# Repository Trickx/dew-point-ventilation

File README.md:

***

# Dew Point Ventilation

**Ventilation is the best and cheapest measure against damp cellars - at least if done right.
In this project, an ESP8266 (NodeMCU) monitors dew points from the inside and outside and activates up to 4 fans to transport the moisture in the air to the outside.**

This project is inspired by 2 articles by the German Make magazine: [Taupunktlüfter](https://github.com/MakeMagazinDE/Taupunktluefter) and [Zirkulationspumpensteuerung](https://github.com/MakeMagazinDE/Zirkulationspumpensteuerung)
Instead of their Arduino approach, this projects makes use of ESP8266 and [Tasmota](https://github.com/arendst/Tasmota).

**Note: I don't take over any risk, nor responsibility for anything. If you decide to reproduce this project you will be killed by hardware or software.**

A PCB was designed with Autodesk's Eagle. The PCB is currently under test, so be aware.

**Diffs from original designs by Make:**
- NodeMCUs instead of Arduino
- Tasmota and Script instead of Arduino coding
- 4 Outputs via solid state relais
- Multiple Sensor options:
- 1Wire
- I2C
- AM230x

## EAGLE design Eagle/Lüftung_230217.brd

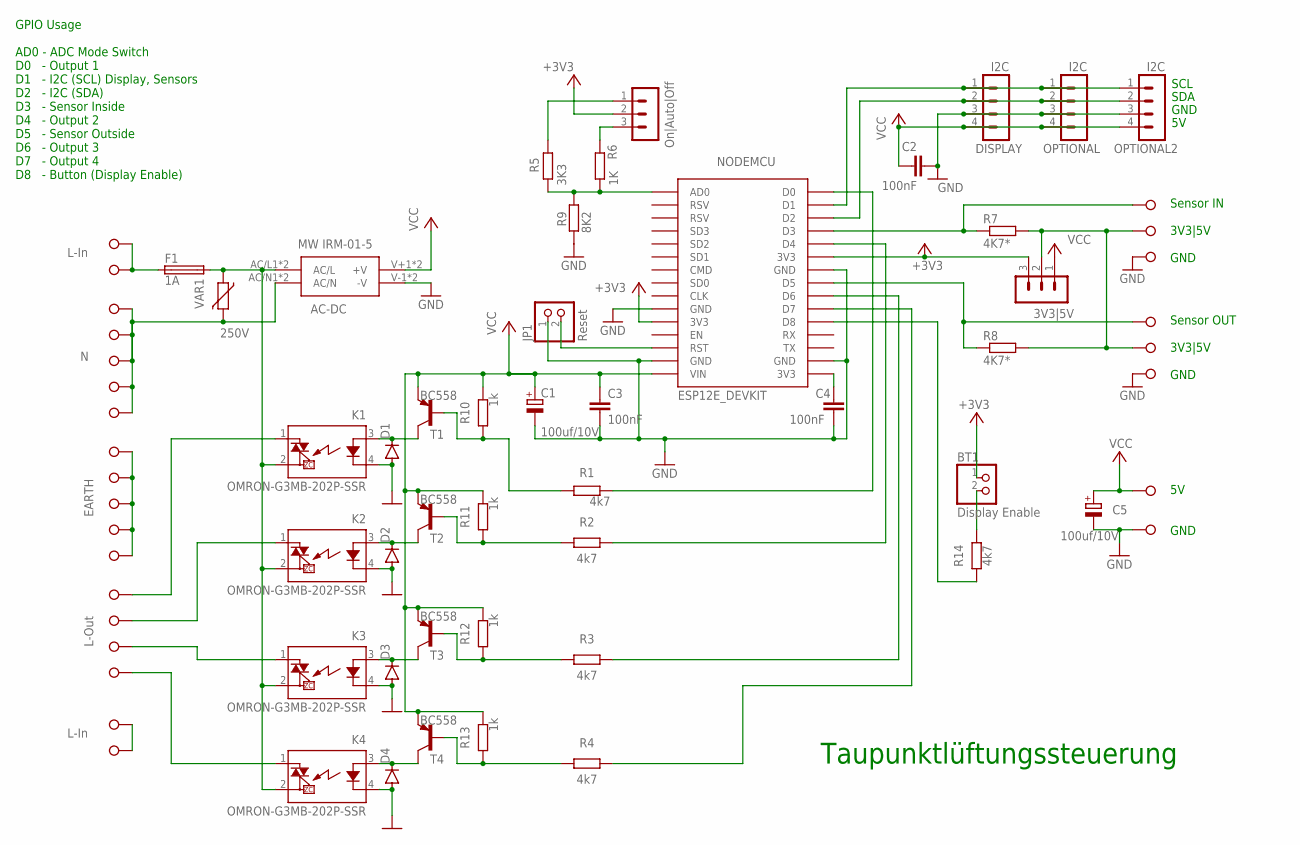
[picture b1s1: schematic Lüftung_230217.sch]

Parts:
5V|3V3: 3V3|5V; LüFTUNG_230217_2_CON-LSTB_MA03-1
AC-DC: MW IRM-01-5; LüFTUNG_230217_2_SAMACSYS_PARTS_IRM015
BT1: Display Enable; LüFTUNG_230217_2_PINHEAD_1X02
C1, C5: 100uf/10V; LüFTUNG_230217_2_MY_RCL_E2,5-7
C2, C3, C4: 100nF; LüFTUNG_230217_2_CAPACITOR-WIMA_C5B3.5
D1: LüFTUNG_230217_2_DIODE_1N4148; LüFTUNG_230217_2_DIODE_D-5
D2, D3, D4: LüFTUNG_230217_2_DIODE_1N4148DO35-7; LüFTUNG_230217_2_DIODE_DO35-7
DISPLAY: I2C; LüFTUNG_230217_2_CON-LSTB_MA04-1
F1: 1A; LüFTUNG_230217_2_MY_FUSE_SH22,5
JP1: Reset; LüFTUNG_230217_2_PINHEAD_1X02
K1, K2, K3, K4: OMRON-G3MB-202P-SSR; LüFTUNG_230217_2_OMRON-G3MB-202P-SSR_OMRON-G3MB-202P-SSR
NODEMCU: ESP12E_DEVKIT; LüFTUNG_230217_2_ESP12E_DEVKIT_ESP12E_DEVKIT
OPTIONAL, OPTIONAL2: I2C; LüFTUNG_230217_2_CON-LSTB_MA04-1
R1, R2, R3, R4, R14: 4k7; LüFTUNG_230217_2_MY_RCL_0207/10
R5: 3K3; LüFTUNG_230217_2_MY_RCL_0204V
R6: 1K; LüFTUNG_230217_2_MY_RCL_0204V
R7, R8: 4K7*; LüFTUNG_230217_2_MY_RCL_0207/10
R9: 8K2; LüFTUNG_230217_2_MY_RCL_0204V
R10, R11, R12, R13: 1k; LüFTUNG_230217_2_MY_RCL_0207/10
SWITCH: On|Auto|Off; LüFTUNG_230217_2_CON-LSTB_MA03-1
T1, T2, T3, T4: BC558; LüFTUNG_230217_2_TRANSISTOR-NEU-TO92_TO92
VAR1: 250V; LüFTUNG_230217_2_MY_VARISTOR_R-5
X1, X18: L-In; CON-WAGO-508_W236-1
X2, X17: L-In; CON-WAGO-508_W236-NOCAP
X3: N; CON-WAGO-508_W236-1
X4, X5, X6, X7: N; CON-WAGO-508_W236-NOCAP
X8: EARTH; CON-WAGO-508_W236-1
X9, X10, X11, X12: EARTH; CON-WAGO-508_W236-NOCAP
X13: L-Out; CON-WAGO-508_W236-1
X14, X15, X16: L-Out; CON-WAGO-508_W236-NOCAP
X19: Sensor-In; CON-WAGO-508_W236-NOCAP
X20, X23: 3V3; CON-WAGO-508_W236-NOCAP
X21, X24: GND; CON-WAGO-508_W236-1
X22: Sensor-Out; CON-WAGO-508_W236-NOCAP
X25: GND; CON-WAGO-508_W236-NOCAP
X26: VCC; CON-WAGO-508_W236-1

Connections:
230V-SWITCH: X17.1, X17.2, X18.1, X18.2
+3V3: 5V|3V3.3, BT1.1, NODEMCU.3V3@0 (3V3), NODEMCU.3V3@1 (3V3), SWITCH.2
EARTH: X8.1, X8.2, X9.1, X9.2, X10.1, X10.2, X11.1, X11.2, X12.1, X12.2
GND: AC-DC.V-1 (-V), AC-DC.V-2 (-V), C1.-, C2.2, C3.2, C4.2, C5.-, D1.A, D2.A, D3.A, D4.A, DISPLAY.3, JP1.1, K1.4 (K), K2.4 (K), K3.4 (K), K4.4 (K), NODEMCU.GND@0 (GND), NODEMCU.GND@1 (GND), NODEMCU.GND@2 (GND), NODEMCU.GND@3 (GND), OPTIONAL.3, OPTIONAL2.3, R9.2, X21.1, X21.2, X24.1, X24.2, X25.1, X25.2
L: F1.1, X1.1, X1.2, X2.1, X2.2
L2: K2.1 (DS1), X14.1, X14.2
L3: K3.1 (DS1), X15.1, X15.2
L4: K4.1 (DS1), X16.1, X16.2
L-OUT: K1.1 (DS1), X13.1, X13.2
LF: AC-DC.AC/L1 (AC/L), AC-DC.AC/L2 (AC/L), F1.2, K1.2 (DS2), K2.2 (DS2), K3.2 (DS2), K4.2 (DS2), VAR1.1
N: AC-DC.AC/N1 (AC/N), AC-DC.AC/N2 (AC/N), VAR1.2, X3.1, X3.2, X4.1, X4.2, X5.1, X5.2, X6.1, X6.2, X7.1, X7.2
unnamed: DISPLAY.1, NODEMCU.D1, OPTIONAL.1, OPTIONAL2.1
unnamed: R1.2, R10.2, T1.2 (B)
unnamed: NODEMCU.D5, R8.1, X22.1, X22.2
unnamed: D1.C, K1.3 (A), T1.3 (C)
unnamed: NODEMCU.D0, R1.1
unnamed: 5V|3V3.2, R7.2, R8.2, X20.1, X20.2, X23.1, X23.2
unnamed: D4.C, K4.3 (A), T4.3 (C)
unnamed: D3.C, K3.3 (A), T3.3 (C)
unnamed: R6.2, SWITCH.3
unnamed: D2.C, K2.3 (A), T2.3 (C)
unnamed: NODEMCU.D4, R2.1
unnamed: NODEMCU.D6, R3.1
unnamed: NODEMCU.D7, R4.1
unnamed: DISPLAY.2, NODEMCU.D2, OPTIONAL.2, OPTIONAL2.2
unnamed: NODEMCU.AD0, R5.1, R6.1, R9.1
unnamed: R5.2, SWITCH.1
unnamed: C4.1, NODEMCU.3V3@2 (3V3)
unnamed: R2.2, R11.2, T2.2 (B)
unnamed: R3.2, R12.2, T3.2 (B)
unnamed: R4.2, R13.2, T4.2 (B)
unnamed: BT1.2, R14.1
unnamed: NODEMCU.D8, R14.2
RST: JP1.2, NODEMCU.RST
SENS_IN: NODEMCU.D3, R7.1, X19.1, X19.2
VCC: 5V|3V3.1, AC-DC.V+1 (+V), AC-DC.V+2 (+V), C1.+, C2.1, C3.1, C5.+, DISPLAY.4, NODEMCU.VIN, OPTIONAL.4, OPTIONAL2.4, R10.1, R11.1, R12.1, R13.1, T1.1 (E), T2.1 (E), T3.1 (E), T4.1 (E), X26.1, X26.2

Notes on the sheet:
Taupunktlüftungssteuerung
Sensor IN 3V3|5V GND
5V GND
Sensor OUT 3V3|5V GND
SCL
SDA
GND
GPIO Usage AD0 - ADC Mode Switch D0 - Output 1 D1 - I2C (SCL) Display, Sensors D2 - I2C (SDA) D3 - Sensor Inside D4 - Output 2 D5 - Sensor Outside D6 - Output 3 D7 - Output 4 D8 - Button (Display Enable)

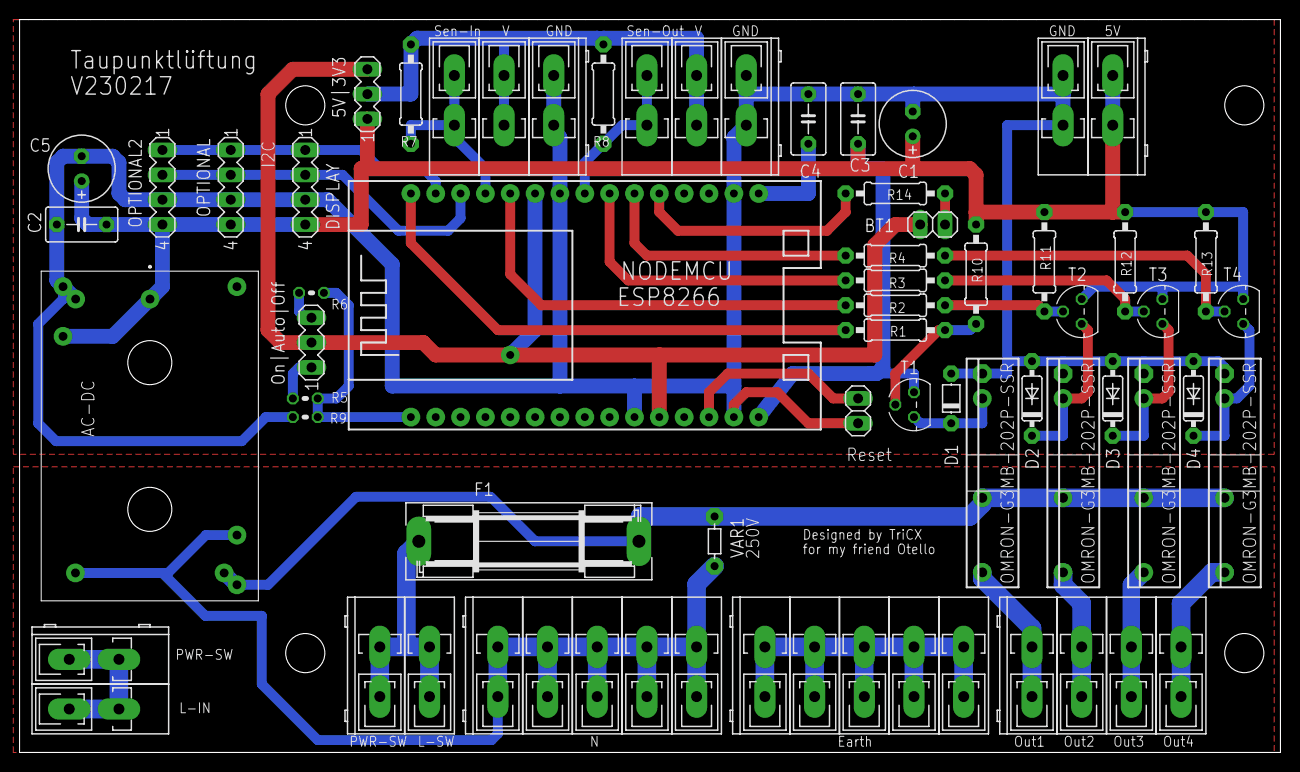
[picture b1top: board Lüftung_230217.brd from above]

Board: 2 copper layers, 128.9 x 74.9 mm, 68 parts (0 on the bottom side), 36 nets.

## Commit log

2023-02-20 Initial Eagle files.
2023-02-20 Initial Tasmota files.
